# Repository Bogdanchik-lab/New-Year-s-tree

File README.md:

# \# Електронна новорічна ялинка (KiCad)

# 

# Проект декоративної друкованої плати у формі новорічної ялинки з мультивібратором для блимання світлодіодами.

# 

# \## 3D-візуалізація плати

# !\[3D-вигляд плати](pcb\_3d.png)

# 

# \## Документація

# \* \*\*Принципова схема:\*\* \[ялинка.pdf](ялинка.pdf)

# \* \*\*Проект розроблено в:\*\* KiCad

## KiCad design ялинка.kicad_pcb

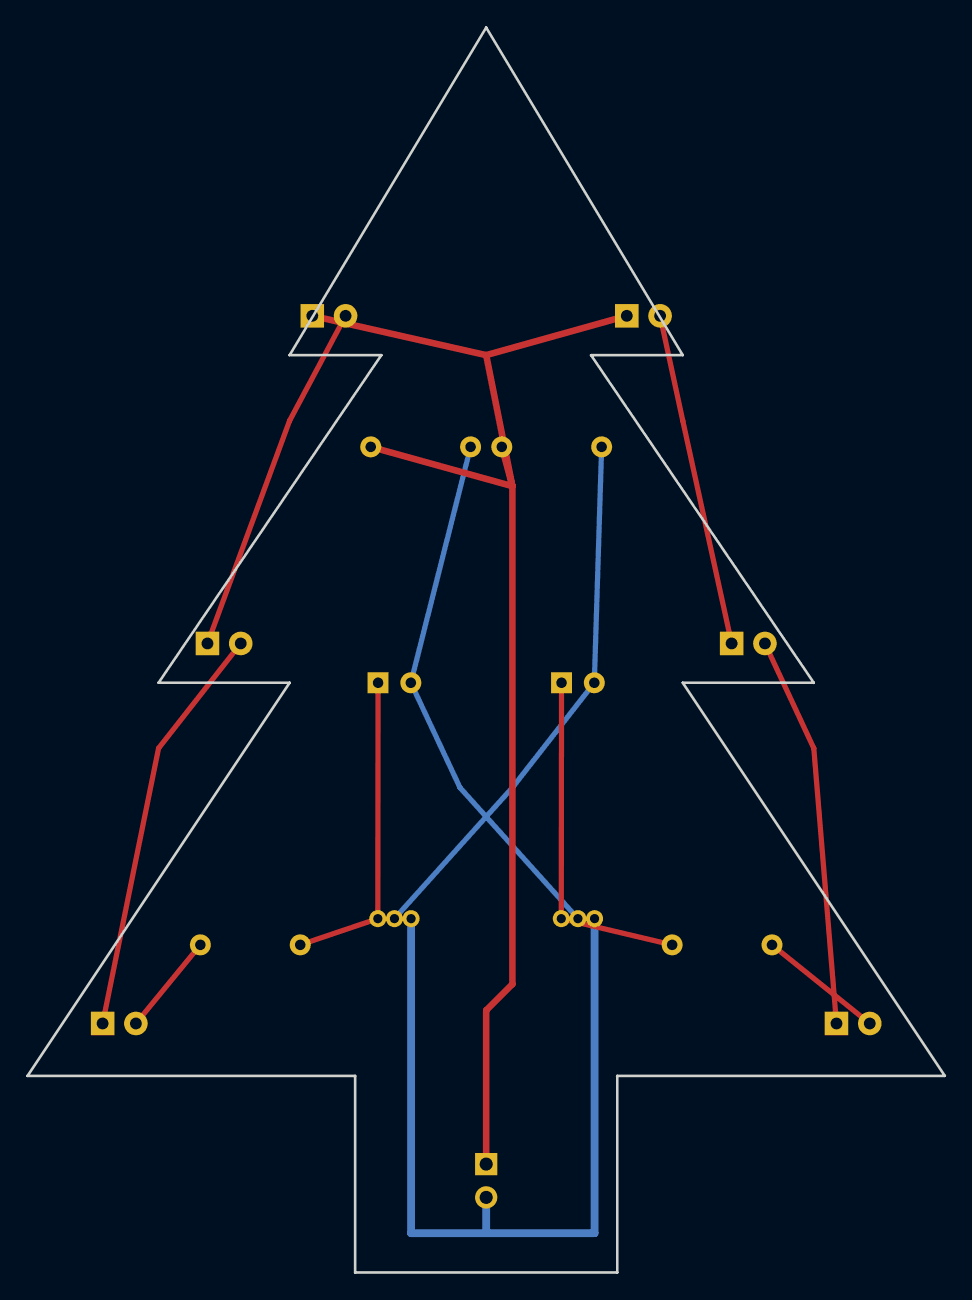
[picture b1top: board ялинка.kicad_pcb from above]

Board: 2 copper layers, 70.0 x 95.0 mm, 15 parts (0 on the bottom side), 12 nets.

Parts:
BT1: PinHeader_1x02_P2.54mm_Vertical
C1, C2: CP_Radial_D5.0mm_P2.50mm
D1, D2, D3, D4, D5, D6: LED_D5.0mm
Q1, Q2: TO-92_Inline
R1, R2, R3, R4: R_Axial_DIN0207_L6.3mm_D2.5mm_P7.62mm_Horizontal

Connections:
GND: BT1.2, Q1.3, Q2.3
unnamed: C1.1, Q1.1, R1.2
unnamed: C1.2, Q2.2, R2.2
unnamed: C2.1, Q2.1, R4.1
unnamed: C2.2, Q1.2, R3.2
unnamed: D1.1, D3.2
unnamed: D3.1, D4.2
unnamed: D2.1, D5.2
unnamed: D5.1, D6.2
unnamed: D1.2, R1.1
unnamed: D2.2, R4.2
VCC: BT1.1, D4.1, D6.1, R2.1, R3.1
